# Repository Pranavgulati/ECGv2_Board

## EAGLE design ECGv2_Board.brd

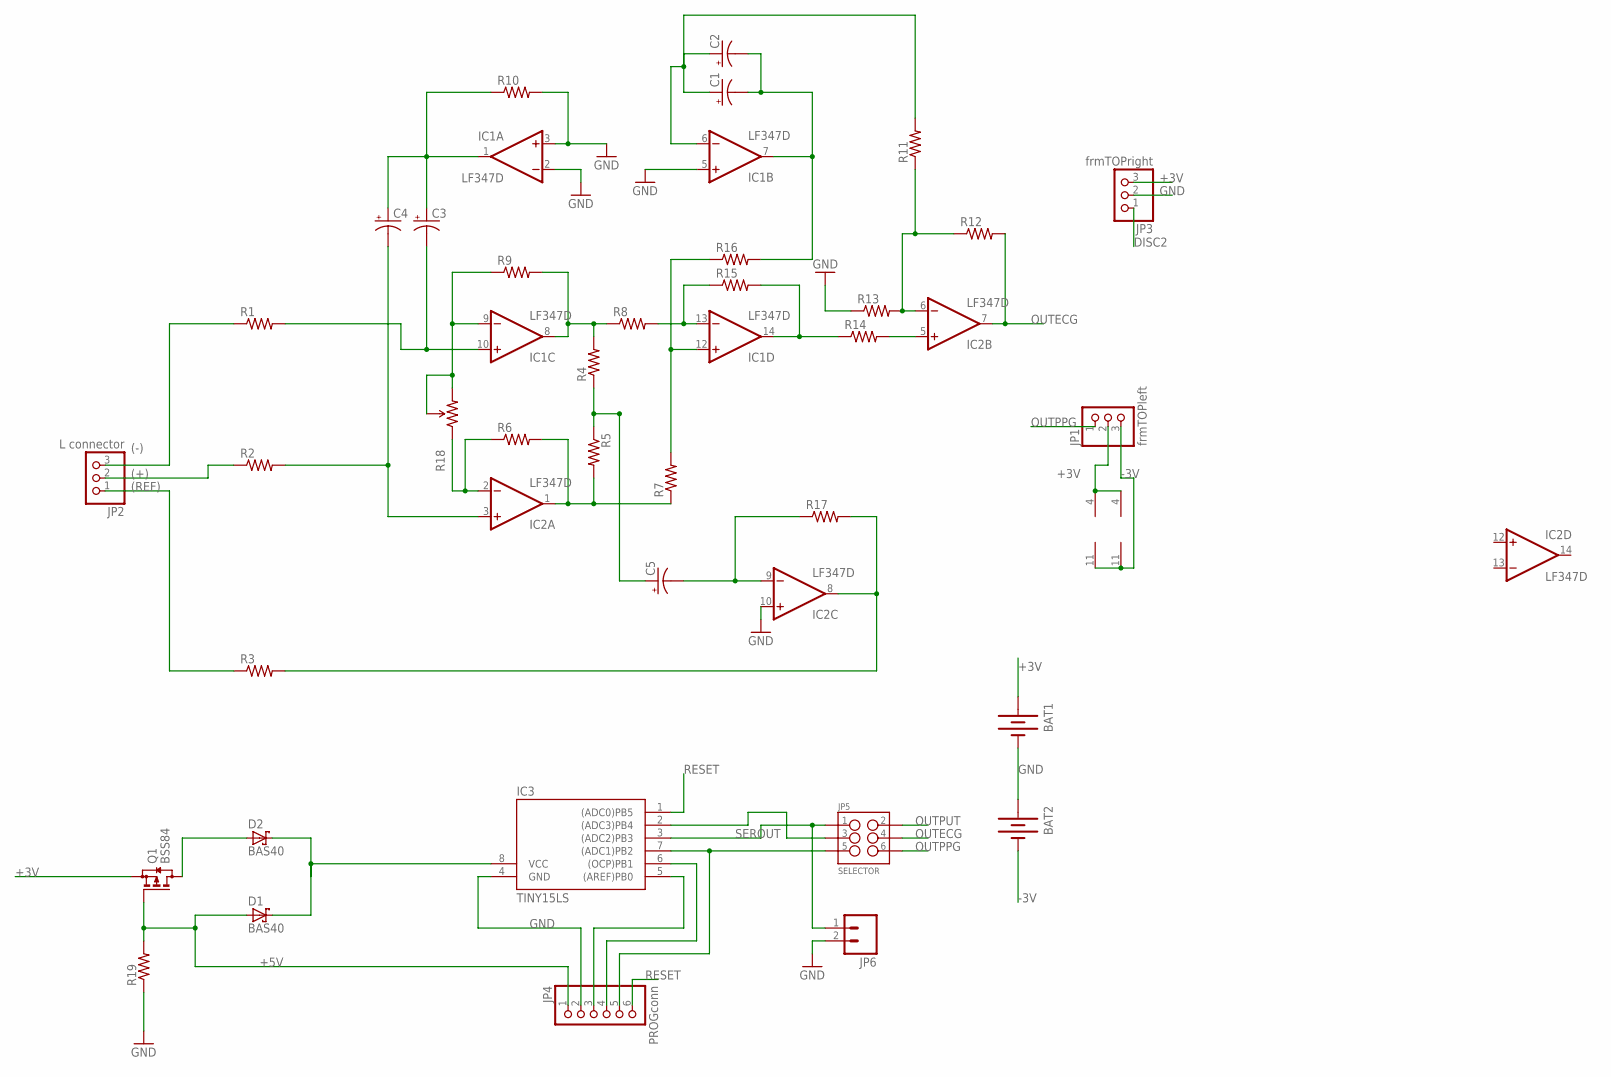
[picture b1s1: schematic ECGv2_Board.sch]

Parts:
BAT1, BAT2: BATTERY245MM; BATTCON_245MM
C1, C2, C3, C4, C5: CAP_POL1206-KIT; EIA3216-KIT
D1, D2: BAS40; SOT23
IC1, IC2: LF347D; SO14
IC3: TINY15LS; SOIC8
JP1: frmTOPleft; 1X03
JP2: L connector; 1X03
JP3: frmTOPright; 1X03
JP4: PROGconn; 1X06-BIG
JP5: SELECTOR; 2X3
JP6: M02PTH; 1X02
Q1: BSS84; SOT23
R1, R2, R3, R4, R5, R6, R7, R8, R9, R10, R11, R12, R13, R14, R15, R16, R17, R19: RESISTOR0402-RES; 0402-RES
R18: TRIMPOT3362U-2; 3362U-2

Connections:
(+): JP2.2, R2.1
(-): JP2.3, R1.1
(REF): JP2.1, R3.1
+3V: BAT1.1 (+), BAT1.3 (+), IC1.4 (V+), IC2.4 (V+), JP1.2, JP3.3, Q1.2 (S)
+5V: D1.1 (A), JP4.1, Q1.1 (G), R19.2
-3V: BAT2.2 (-), IC1.11 (V-), IC2.11 (V-), JP1.3
DISC2: JP3.1
GND: BAT1.2 (-), BAT2.1 (+), BAT2.3 (+), IC1.2 (-IN), IC1.3 (+IN), IC1.5 (+IN), IC2.10 (+IN), IC3.4 (GND), JP3.2, JP4.2, JP6.2, R10.2, R13.1, R19.1
unnamed: C1.C (-), C2.C (-), IC1.7 (OUT), R16.2
unnamed: C1.A (+), C2.A (+), IC1.6 (-IN), R11.2
unnamed: IC1.9 (-IN), R9.1, R18.2 (WIPER), R18.3 (CW)
unnamed: D2.1 (A), Q1.3 (D)
unnamed: IC2.6 (-IN), R11.1, R12.1, R13.2
unnamed: IC1.14 (OUT), R14.1, R15.2
unnamed: IC1.13 (-IN), R8.2, R15.1
unnamed: IC1.12 (+IN), R7.2, R16.1
unnamed: IC2.1 (OUT), R5.2, R6.2, R7.1
unnamed: IC1.8 (OUT), R4.2, R8.1, R9.2
unnamed: IC2.2 (-IN), R6.1, R18.1 (CCW)
unnamed: C5.A (+), R4.1, R5.1
unnamed: C5.C (-), IC2.9 (-IN), R17.1
unnamed: IC2.8 (OUT), R3.2, R17.2
unnamed: C3.A (+), C4.A (+), IC1.1 (OUT), R10.1
unnamed: IC2.5 (+IN), R14.2
unnamed: C4.C (-), IC2.3 (+IN), R2.2
unnamed: C3.C (-), IC1.10 (+IN), R1.2
unnamed: IC3.5 ((AREF)PB0), JP4.3
unnamed: IC3.6 ((OCP)PB1), JP4.4
unnamed: IC3.7 ((ADC1)PB2), JP4.5, JP5.5
unnamed: D1.3 (C), D2.3 (C), IC3.8 (VCC)
unnamed: IC3.2 ((ADC3)PB4), JP5.3
OUTECG: IC2.7 (OUT), JP5.4, R12.2
OUTPPG: JP1.1, JP5.6
OUTPUT: JP5.2
RESET: IC3.1 ((ADC0)PB5), JP4.6
SEROUT: IC3.3 ((ADC2)PB3), JP5.1, JP6.1

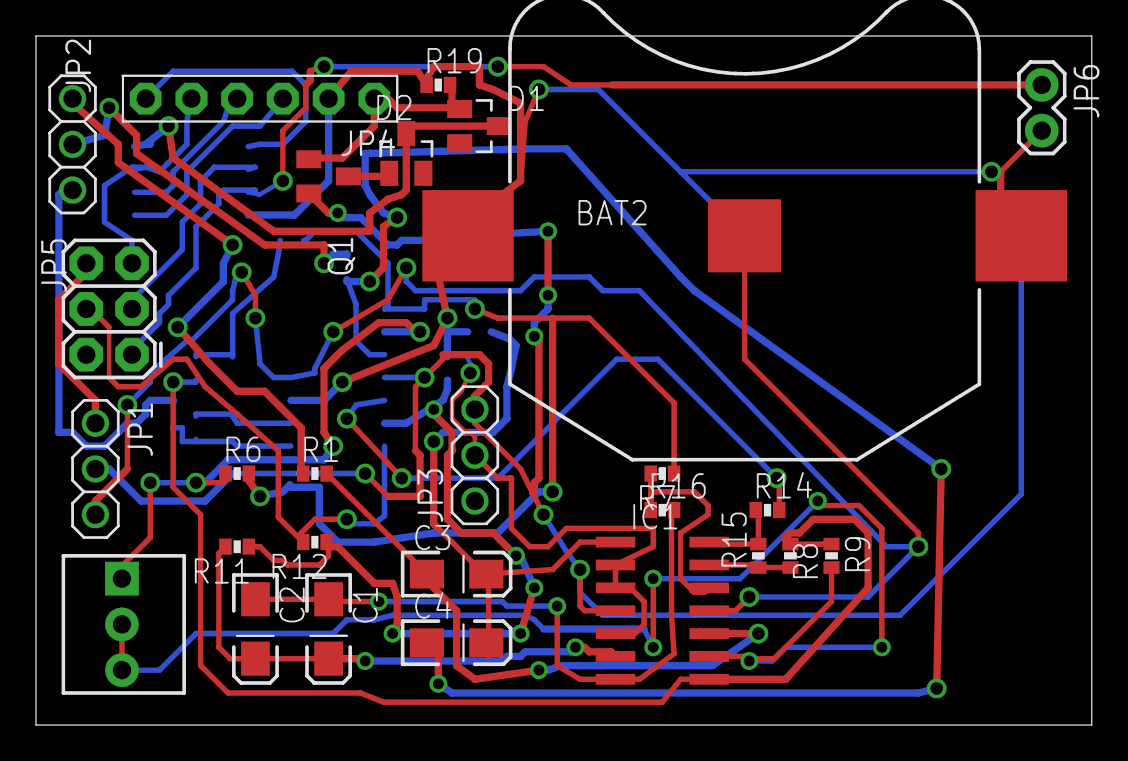
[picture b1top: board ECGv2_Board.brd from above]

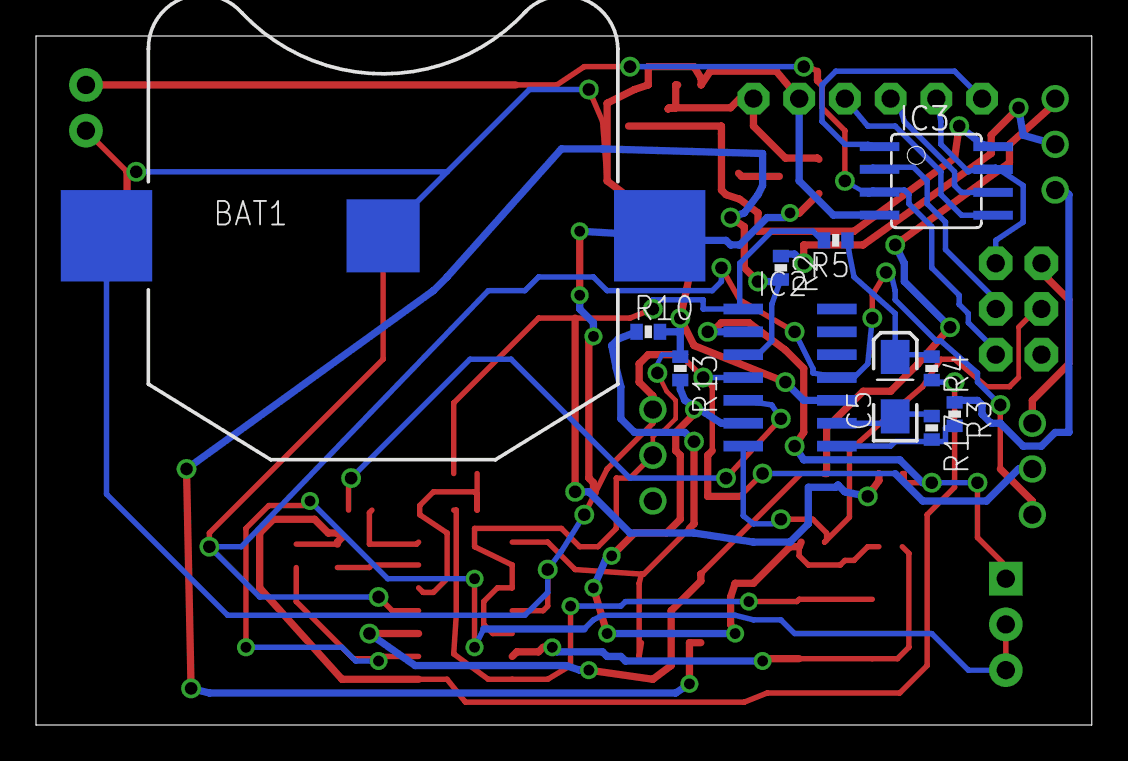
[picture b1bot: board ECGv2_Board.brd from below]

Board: 2 copper layers, 58.7 x 38.3 mm, 38 parts (11 on the bottom side), 34 nets.

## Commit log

2016-03-23 :neckbeard: Added .gitattributes
2016-03-23 Final commit
    -done PCB routing and schematic completely
    - added selector jumpers
    -auto switch between power and battery for MCU only
    -added programming connectors
2016-06-01 -added missing connection
2016-06-09 Major changes
    -final commit
    -some corrections
2016-07-06 -restructuring
    -identification and restructuring of circuit
2016-08-13 -restructuring

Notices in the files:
parts and their libraries:
SparkFun-Passives: Licensing: Creative Commons ShareAlike 4.0 International - https://creativecommons.org/licenses/by-sa/4.0
